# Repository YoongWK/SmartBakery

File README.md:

# Smart Bakery

The Smart Bakery system is a comprehensive solution for monitoring and controlling temperature and humidity within a bakery. Using a Raspberry Pi Model 3B with a BME280 module, the system publishes data from the bakery to a Flask server via MQTT for storage in an InfluxDB V3.0 Cloud Serverless database. Users can view the bakery data via a Web Dashboard created using HTML, CSS, and JavaScript.

The dashboard also allows users to set temperature thresholds, control heating (Bulb) and cooling (Fan) devices, and activate/deactivate a buzzer alert for extreme temperatures. Moreover, an RGB LED provides a clear visual indication of the current operational status for floor managers in the bakery. Additionally, the system can operate automatically where fan speed and bulb heat levels are adjusted according to the current temperature or manually for direct user control.

By providing real-time environmental tracking and responsive control, the system can maintain optimal conditions in the bakery for high-quality baked goods.

<br />

## Instructions for Raspberry Pi Model 3B Setup
> Step 1: Fabricate the PCB using the gerber files in EAGLE\PCB\SmartBakerySensor

> Step 2: Assemble the PCB

> Step 3: Connect the PCB to the Raspberry Pi Model 3B

> Step 4: Run the Smart_Bakery_Sensor.py Python script in the the Raspberry Pi Model 3B

<br />

## Instructions for Dashboard Setup
> Step 1: Download the app

```bash
git clone https://github.com/YoongWK/SmartBakery.git
cd SmartBakery
```

> Step 2: Enter your MQTT & InfluxDB V3.0 Cloud Serverless details in the .env.example file

> Step 3: Rename the .env.example file to .env

> Step 4: Create the Python virtual environment

```bash
python -m venv .venv
```

> Step 5: Set the execution policy of the current user to unrestricted

```bash
Set-ExecutionPolicy -ExecutionPolicy Unrestricted  -Scope CurrentUser
```

> Step 6: Activate the virtual environment

```bash
.venv\Scripts\activate
```

> Step 7: Install the required libraries into the virtual environment

```bash
pip install -r requirements.txt
```

> Step 8: Run the app

```bash
python app.py
```

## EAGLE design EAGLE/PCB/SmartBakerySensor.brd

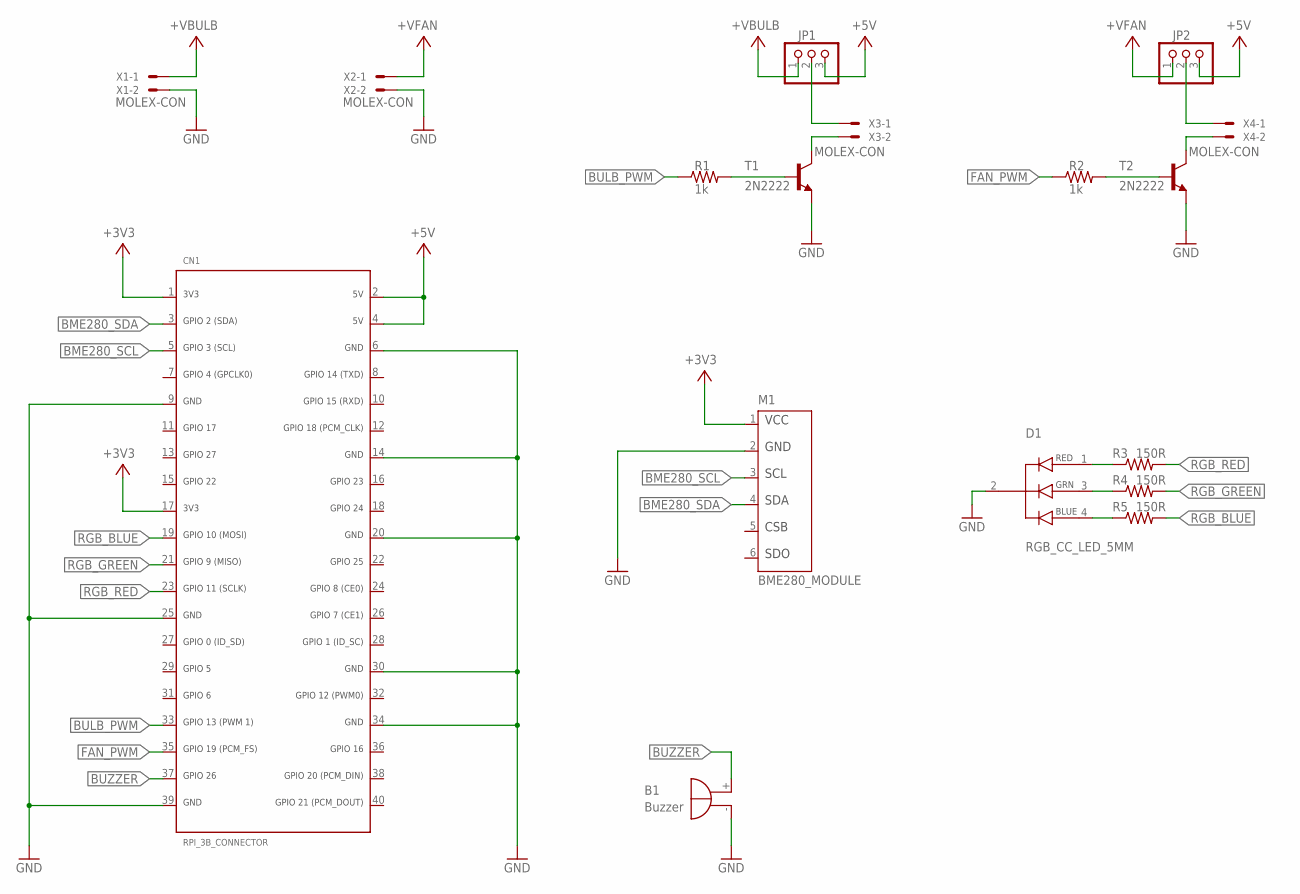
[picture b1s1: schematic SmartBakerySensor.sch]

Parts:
B1: Buzzer; F/TMB
CN1: RPI_3B_CONNECTOR; RPI_3B_CONNECTOR_FOOTPRINT
D1: RGB_CC_LED_5MM; RGB_CC_LED_FOOTPRINT
JP1, JP2: PINHD-1X3; 1X03
M1: BME280_MODULE; BME280_FOOTPRINT
R1, R2: 1k; R0805
R3, R4, R5: 150R; R0805
T1, T2: 2N2222; TO92-EBC
X1, X2, X3, X4: MOLEX-CON; 22-23-2021

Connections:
+3V3: CN1.1, CN1.17, M1.1
+5V: CN1.2, CN1.4, JP1.3, JP2.3
BME280_SCL: CN1.5, M1.3
BME280_SDA: CN1.3, M1.4
BULB_PWM: CN1.33, R1.1
BUZZER: B1.+, CN1.37
FAN_PWM: CN1.35, R2.1
GND: B1.-, CN1.6, CN1.9, CN1.14, CN1.20, CN1.25, CN1.30, CN1.34, CN1.39, D1.2, M1.2, T1.E, T2.E, X1.2, X2.2
unnamed: D1.1, R3.1
unnamed: D1.3, R4.1
unnamed: D1.4, R5.1
unnamed: R2.2, T2.B
unnamed: R1.2, T1.B
unnamed: T1.C, X3.2
unnamed: T2.C, X4.2
unnamed: JP1.2, X3.1
unnamed: JP2.2, X4.1
RGB_BLUE: CN1.19, R5.2
RGB_GREEN: CN1.21, R4.2
RGB_RED: CN1.23, R3.2
V+: JP2.1, X2.1
VCC: JP1.1, X1.1

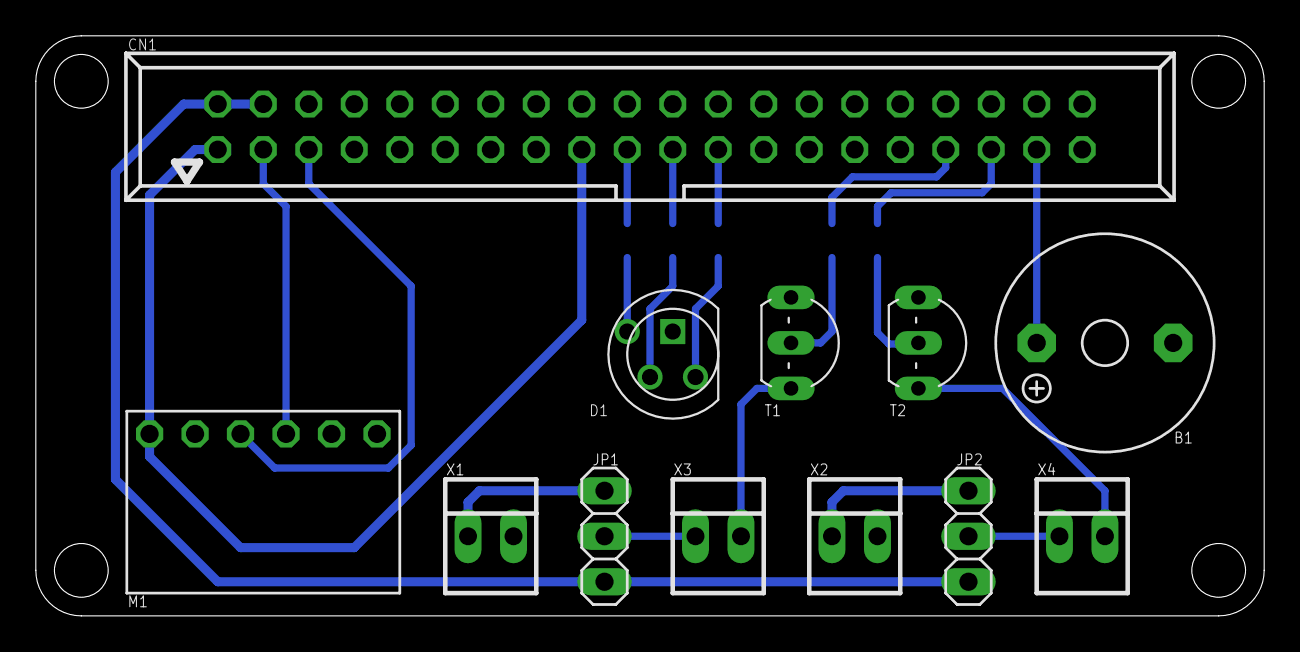
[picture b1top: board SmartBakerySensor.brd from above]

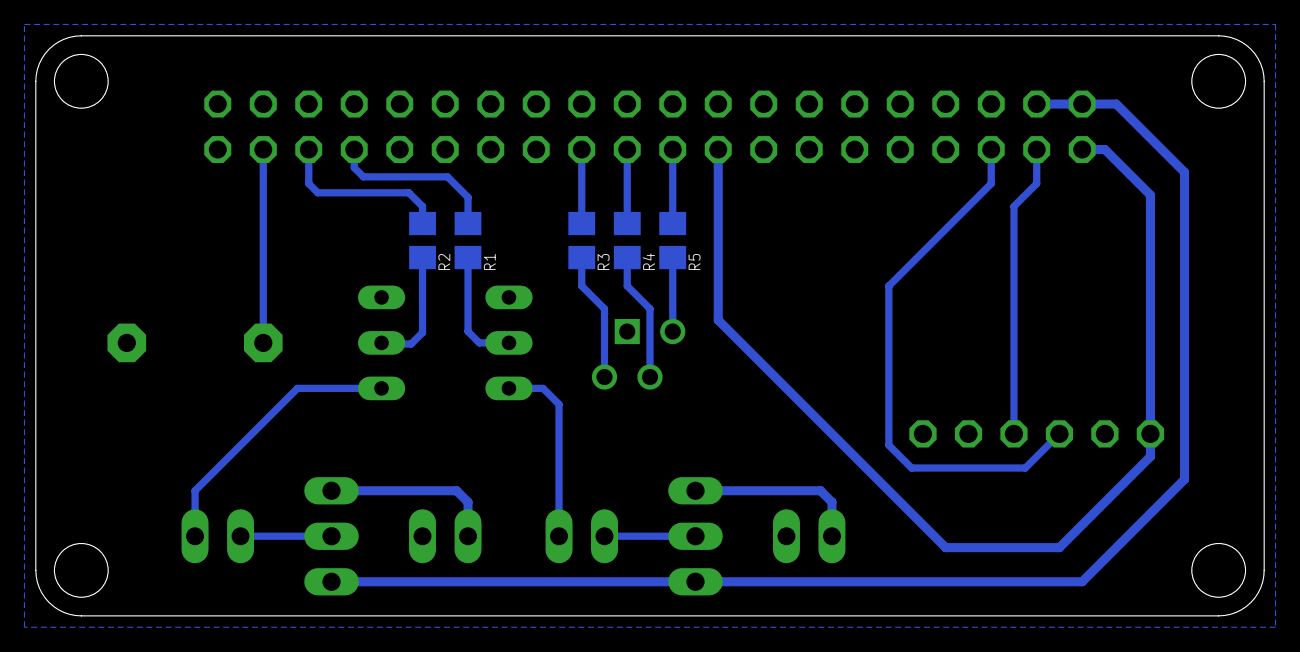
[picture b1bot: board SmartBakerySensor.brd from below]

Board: 2 copper layers, 68.6 x 32.4 mm, 17 parts (5 on the bottom side), 22 nets.

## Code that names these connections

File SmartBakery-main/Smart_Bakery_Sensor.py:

#-------------------------------------------- Header Start ---------------------------------------------#
"""
    Project Title: Smart Bakery System
    Project Class: IOTP - PE04
    Project Group: 06
    Project Developers: Andrina Wei Ning Morrison, Ryan Chong Jay Chin, Yoong Wai Kit
    Project Development Period: Nov 2023 - Feb 2024
"""
#--------------------------------------------- Header End ----------------------------------------------#

#-------------------------------------------- Imports Start --------------------------------------------#
import time
import threading
from datetime import datetime
import RPi.GPIO as GPIO
import paho.mqtt.client as mqtt
import smbus2
import bme280
#--------------------------------------------- Imports End ---------------------------------------------#

#------------------------------------- RPI Pin Configuration Start -------------------------------------#
# RPI GPIO PIN Assignment
RED_LED_PIN = 11
GREEN_LED_PIN = 9
BLUE_LED_PIN = 10
BULB_PWM_PIN = 13
FAN_PWM_PIN = 19
BUZZER_PIN = 26

# RPI GPIO PIN Setting
GPIO.setmode(GPIO.BCM)
GPIO.setup(RED_LED_PIN, GPIO.OUT)
GPIO.setup(GREEN_LED_PIN, GPIO.OUT)
GPIO.setup(BLUE_LED_PIN, GPIO.OUT)
GPIO.setup(BULB_PWM_PIN, GPIO.OUT)
GPIO.setup(FAN_PWM_PIN, GPIO.OUT)
GPIO.setup(BUZZER_PIN, GPIO.OUT)
BULB = GPIO.PWM(BULB_PWM_PIN, 100)
FAN = GPIO.PWM(FAN_PWM_PIN, 100)
#-------------------------------------- RPI Pin Configuration End --------------------------------------#

#------------------------------------------- Variables Start -------------------------------------------#
# Program Variable
run_program = True

# MQTT Variables
mqtt_broker = 'test.mosquitto.org'
topic_data = 'iotp/proj/grp06/sensordata'
topic_control = 'iotp/proj/grp06/sensorcontrol'

# BME280 Variables
bus = smbus2.SMBus(bus=1)
address = 0x76
calibration_params = bme280.load_calibration_params(bus=bus, address=address)

# Smart Bakery Variables
low_temp = 27
high_temp = 29
rgb_color = ""
fan_speed = 0
bulb_heat = 0
buzzer_enabled = 1
buzzer_state = 0
manual_state = 0
#-------------------------------------------- Variables End --------------------------------------------#

#------------------------------------------- Functions Start -------------------------------------------#

# This function sets the RGB Led according to the color input
def setRGBLEDColor(color):
    if color == "blue":
        GPIO.output(RED_LED_PIN, GPIO.LOW) #red low
        GPIO.output(GREEN_LED_PIN, GPIO.LOW) #green low
        GPIO.output(BLUE_LED_PIN, GPIO.HIGH) #blue high
    elif color == "green":
        GPIO.output(RED_LED_PIN, GPIO.LOW) #red low
        GPIO.output(GREEN_LED_PIN, GPIO.HIGH) #green high
        GPIO.output(BLUE_LED_PIN, GPIO.LOW) #blue low
    elif color == "red":
        GPIO.output(RED_LED_PIN, GPIO.HIGH) #red high
        GPIO.output(GREEN_LED_PIN, GPIO.LOW) #green low
        GPIO.output(BLUE_LED_PIN, GPIO.LOW) #blue low
    else:
        GPIO.output(RED_LED_PIN, GPIO.LOW) #red low
        GPIO.output(GREEN_LED_PIN, GPIO.LOW) #green low
        GPIO.output(BLUE_LED_PIN, GPIO.LOW) #blue

# This calculates the PWM speed
def calculateLevel(value, max_level, step):
    return min(int(value // step) + 1, max_level)

# This sets the bulb heat / power using PWM
def setBulbHeat(heat, max_level):
    BULB.ChangeDutyCycle(max(min(heat * (100 / max_level), 100), 0))

# This sets the fan speed / power using PWM
def setFanSpeed(speed, max_level):
    FAN.ChangeDutyCycle(max(min(speed * (100 / max_level), 100), 0))

# This sets the buzzer state
def setBuzzerState(state):
    GPIO.output(BUZZER_PIN, GPIO.LOW if (state == 0) else GPIO.HIGH)

# This sets up the Raspberry Pi according to the commands retrieved from the dashboard
def onMessage(client, userdata, message):
    global manual_state, fan_speed, bulb_heat, buzzer_enabled, low_temp, high_temp
    payload = message.payload.decode('utf-8')
    print(f"\nReceived command: {payload}")
    
    if "manualstate" in payload:
        manual_state = int(payload.split(',')[1])
    elif "fanspeed" in payload:
        fan_speed = int(payload.split(',')[1])
    elif "bulbheat" in payload:
        bulb_heat = int(payload.split(',')[1])
    elif "buzzerenabled" in payload:
        buzzer_enabled = int(payload.split(',')[1])
    elif "lowtemp" in payload:
        low_temp = float(payload.split(',')[1])
    elif "hightemp" in payload:
        high_temp = float(payload.split(',')[1])

# This starts the MQTT Subscriber that retrieves the Sensor Commands throught the 'topic_control' topic
def startMQTTSubscriber():
    mqtt_subscriber = mqtt.Client()
    mqtt_subscriber.on_message = onMessage
    mqtt_subscriber.connect(host=mqtt_broker, port=1883)
    mqtt_subscriber.subscribe(topic=topic_control, qos=1)
    mqtt_subscriber.loop_start()

# This starts the MQTT Publisher that publishes the sensor data through the 'topic_data' topic
# This function also handles the onboard device response to sensor data changes
def startMQTTPublisher():
    global rgb_color, fan_speed, bulb_heat, buzzer_state
    
    while run_program:
        date_time = datetime.now()
        data = bme280.sample(bus=bus, address=address, compensation_params=calibration_params)
        
        # This sets up the onboard devices according to the latest temperature readings
        if data.temperature >= high_temp:
            rgb_color = "red"
            if manual_state == 0:
                fan_speed = calculateLevel(value=(data.temperature - high_temp), max_level=5, step=0.5)
                bulb_heat = 0
            buzzer_state = 1
        elif data.temperature < low_temp:
            rgb_color = "blue"
            if manual_state == 0:
                fan_speed = 0
                bulb_heat = calculateLevel(value=(low_temp - data.temperature), max_level=5, step=0.5)
            buzzer_state = 1
        else:
            rgb_color = "green"
            if manual_state == 0:
                fan_speed = 0
                bulb_heat = 0
            buzzer_state = 0
        
        # Initialises the MQTT Publisher
        mqtt_publisher = mqtt.Client()
        mqtt_publisher.connect(host=mqtt_broker, port=1883)
        print(f"\nClient was created at {date_time.strftime('%H:%M:%S')}")
        
        # Publishes Sensor Data
        try:
            payload = f"{date_time},{data.temperature:.02f},{data.humidity:.02f},{fan_speed},{bulb_heat},{manual_state},{buzzer_state},{buzzer_enabled},{low_temp:.01f},{high_temp:.01f}"
            mqtt_publisher.publish(topic=topic_data, payload=payload, qos=1)
            print(f"Sent record: {payload}")
        except Exception as e:
            print(f"Error publishing\n{e}")
        else:
            mqtt_publisher.disconnect()
            print("Disconnected from broker")
        
        time.sleep(1)
#-------------------------------------------- Functions End --------------------------------------------#

#------------------------------------- RPI Pin Initialisation Start ------------------------------------#
setRGBLEDColor(color=rgb_color)
BULB.start(0)
FAN.start(0)
setBuzzerState(state=buzzer_state)
#-------------------------------------- RPI Pin Initialisation End -------------------------------------#

#------------------------------------------ Main Program Start -----------------------------------------#
subscriberThread = threading.Thread(target=startMQTTSubscriber)
subscriberThread.start()

publisherThread = threading.Thread(target=startMQTTPublisher)
publisherThread.start()

try:
    while run_program:        
        setRGBLEDColor(color=rgb_color)
        setBulbHeat(heat=bulb_heat, max_level=5)
        setFanSpeed(speed=fan_speed, max_level=5)
        setBuzzerState(state=buzzer_state if buzzer_enabled else 0)
        time.sleep(0.2)
except KeyboardInterrupt:
    run_program = False
except Exception as e:
    run_program = False
    print(e)
finally:
    GPIO.cleanup()
    print("\nGPIO cleaned up")
#------------------------------------------- Main Program End ------------------------------------------#

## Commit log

2024-01-17 Updated Settings Card In Dashboard.
2024-01-18 Edited Settings Card
2024-01-22 Added Temperature, Humidity, Bulb Heat, & Fan Speed Time Series Graph.
2024-01-22 Fixed Bug With Zero Line On Graph.
2024-02-10 Commented code and added EAGLE PCB files.
